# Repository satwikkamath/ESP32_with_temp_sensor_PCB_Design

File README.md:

# ESP32-S3 PCB Design with Temperature Sensor and RGB LED

## Overview

This project focuses on designing a custom PCB using the **ESP32-S3-MINI-1-N8** microcontroller. The PCB integrates an **ENS210** temperature and humidity sensor, a **WS2812B RGB LED** for visual feedback, and a power regulation system using the **TLV75801 LDO** voltage regulator. The design also includes **TVS protection diodes** for USB input safety.

The PCB was designed using **KiCad** and is tailored for applications that require environmental sensing and LED indication, powered through USB with proper surge protection.

## Features

- **ESP32-S3-MINI-1-N8**: A powerful microcontroller for managing sensors, RGB LED, and communication.
- **ENS210 Temperature & Humidity Sensor**: Provides accurate temperature and humidity readings.
- **WS2812B RGB LED**: Addressable LED for visual indication based on temperature readings.
- **TLV75801 LDO Regulator**: Provides a stable 3.3V output from the USB 5V input.
- **USB Surge Protection**: Includes **D3V3XA4B10LP TVS diodes** for protecting the USB input from overvoltage or surge.

## Schematic Design

The schematic was created using **KiCad** and includes the following blocks:

1. **ESP32-S3 Microcontroller**: 
   - Handles the processing and communication.
   - I²C interface to the ENS210 sensor.
   - GPIO control for the WS2812B RGB LED.

2. **ENS210 Temperature & Humidity Sensor**:
   - Connected via the I²C bus.
   - Powered by 3.3V from the regulator.

3. **WS2812B RGB LED**:
   - Data pin connected to GPIO48 of the ESP32.
   - Powered by the 3.3V rail.

4. **TLV75801 LDO**:
   - Regulates 5V USB input to a stable 3.3V output for all components.

5. **TVS Diodes**:
   - Protect the USB power input from surges.

## PCB Layout

The PCB layout includes:

- **Compact design**: Minimizes the space required while keeping all components well-organized.
- **Optimized power and ground planes**: Ensures stable operation and reduces noise.
- **Via stitching**: Improves ground plane integrity.
- **Thermal relief pads**: Used for better heat dissipation where needed.
- **USB Input Protection**: TVS diodes are placed near the USB input to provide surge protection.

# STATUS: ONGOING

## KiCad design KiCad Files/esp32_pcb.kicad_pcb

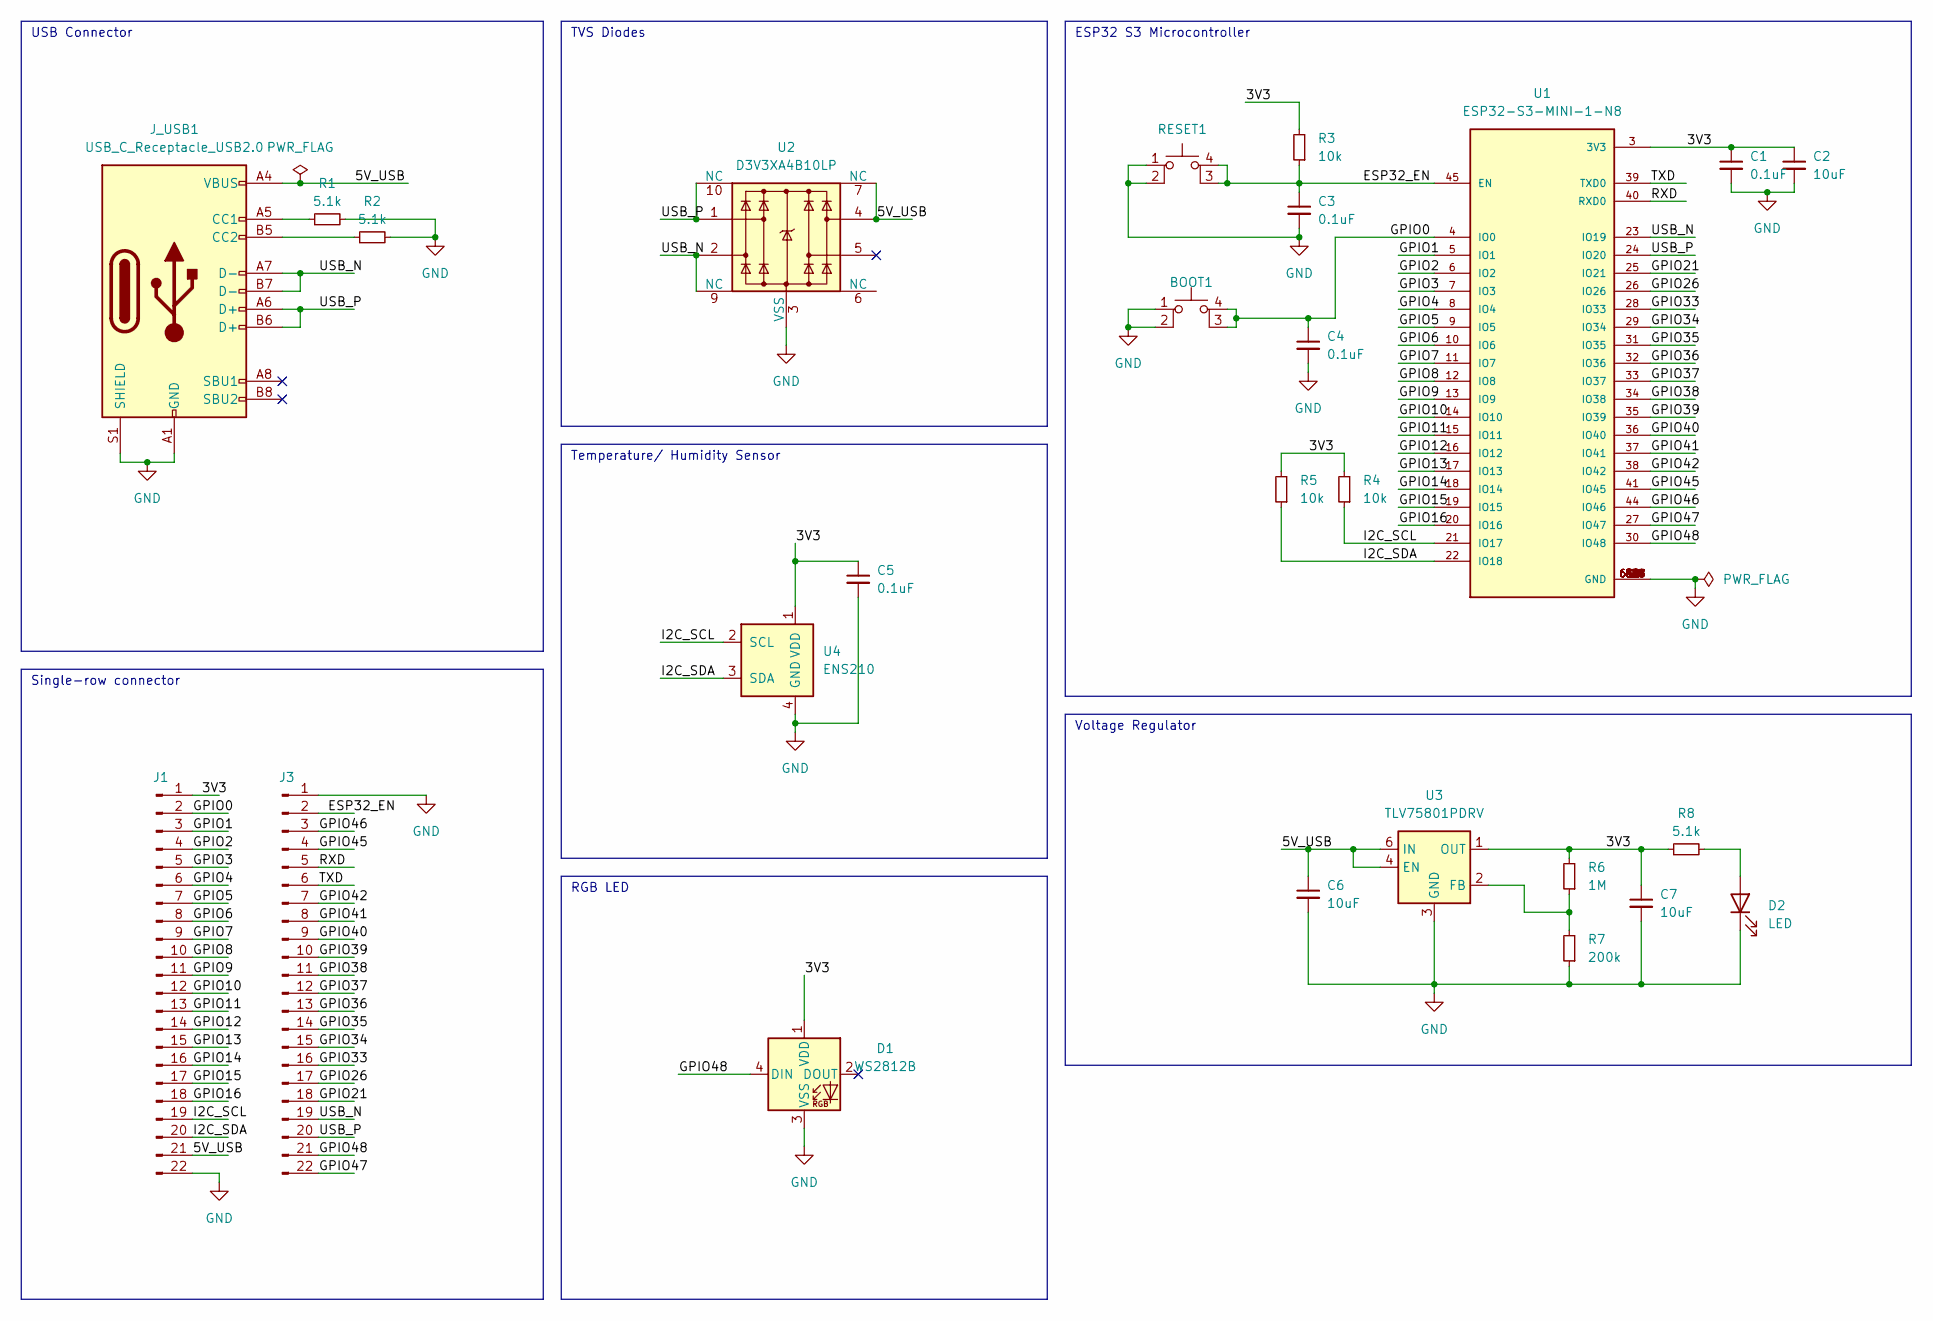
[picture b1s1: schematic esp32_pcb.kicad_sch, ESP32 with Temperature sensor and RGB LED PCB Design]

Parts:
BOOT1: SW_SPST_PTS810
C1, C3, C4, C5: 0.1uF; C_0603_1608Metric
C2, C6, C7: 10uF; C_0603_1608Metric
D1: WS2812B; LED_WS2812B_PLCC4_5.0x5.0mm_P3.2mm
D2: LED; LED_0603_1608Metric
J1: PinHeader_1x22_P2.54mm_Vertical
J3: Conn_01x22_Pin; PinHeader_1x22_P2.54mm_Vertical
J_USB1: USB_C_Receptacle_USB2.0; USB_C_Receptacle_GCT_USB4105-xx-A_16P_TopMnt_Horizontal
R1, R2, R8: 5.1k; R_0603_1608Metric
R3, R4, R5: 10k; R_0603_1608Metric
R6: 1M; R_0603_1608Metric
R7: 200k; R_0603_1608Metric
RESET1: SW_SPST_PTS810
U1: ESP32-S3-MINI-1-N8; XCVR_ESP32-S3-MINI-1-N8; PARTREV v0.6
U2: D3V3XA4B10LP; Diodes_UDFN-10_1.0x2.5mm_P0.5mm
U3: TLV75801PDRV; WSON-6-1EP_2x2mm_P0.65mm_EP1x1.6mm
U4: ENS210; AMS_QFN-4-1EP_2x2mm_P0.95mm_EP0.7x1.6mm

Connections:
/3V3: C1.1, C2.1, C5.1, C7.1, D1.1 (VDD), J1.1, R3.2, R4.2, R5.2, R6.2, R8.1, U1.3 (3V3), U3.1 (OUT), U4.1 (VDD)
/5V_USB: C6.1, J1.21, J_USB1.A4 (VBUS), J_USB1.A9 (VBUS), J_USB1.B4 (VBUS), J_USB1.B9 (VBUS), U2.4, U2.7 (NC), U3.4 (EN), U3.6 (IN)
/ESP32_EN: C3.1, J3.2, R3.1, RESET1.3 (K), RESET1.4 (A), U1.45 (EN)
/GPIO0: BOOT1.3 (K), BOOT1.4 (A), C4.1, J1.2, U1.4 (IO0)
/GPIO1: J1.3, U1.5 (IO1)
/GPIO2: J1.4, U1.6 (IO2)
/GPIO3: J1.5, U1.7 (IO3)
/GPIO4: J1.6, U1.8 (IO4)
/GPIO5: J1.7, U1.9 (IO5)
/GPIO6: J1.8, U1.10 (IO6)
/GPIO7: J1.9, U1.11 (IO7)
/GPIO8: J1.10, U1.12 (IO8)
/GPIO9: J1.11, U1.13 (IO9)
/GPIO10: J1.12, U1.14 (IO10)
/GPIO11: J1.13, U1.15 (IO11)
/GPIO12: J1.14, U1.16 (IO12)
/GPIO13: J1.15, U1.17 (IO13)
/GPIO14: J1.16, U1.18 (IO14)
/GPIO15: J1.17, U1.19 (IO15)
/GPIO16: J1.18, U1.20 (IO16)
/GPIO21: J3.18, U1.25 (IO21)
/GPIO26: J3.17, U1.26 (IO26)
/GPIO33: J3.16, U1.28 (IO33)
/GPIO34: J3.15, U1.29 (IO34)
/GPIO35: J3.14, U1.31 (IO35)
/GPIO36: J3.13, U1.32 (IO36)
/GPIO37: J3.12, U1.33 (IO37)
/GPIO38: J3.11, U1.34 (IO38)
/GPIO39: J3.10, U1.35 (IO39)
/GPIO40: J3.9, U1.36 (IO40)
/GPIO41: J3.8, U1.37 (IO41)
/GPIO42: J3.7, U1.38 (IO42)
/GPIO45: J3.4, U1.41 (IO45)
/GPIO46: J3.3, U1.44 (IO46)
/GPIO47: J3.22, U1.27 (IO47)
/GPIO48: D1.4 (DIN), J3.21, U1.30 (IO48)
/I2C_SCL: J1.19, R4.1, U1.21 (IO17), U4.2 (SCL)
/I2C_SDA: J1.20, R5.1, U1.22 (IO18), U4.3 (SDA)
/RXD: J3.5, U1.40 (RXD0)
/TXD: J3.6, U1.39 (TXD0)
/USB_N: J3.19, J_USB1.A7 (D-), J_USB1.B7 (D-), U1.23 (IO19), U2.2, U2.9 (NC)
/USB_P: J3.20, J_USB1.A6 (D+), J_USB1.B6 (D+), U1.24 (IO20), U2.1, U2.10 (NC)
GND: BOOT1.1, BOOT1.2, C1.2, C2.2, C3.2, C4.2, C5.2, C6.2, C7.2, D1.3 (VSS), D2.1 (K), J1.22, J3.1, J_USB1.A1 (GND), J_USB1.A12 (GND), J_USB1.B1 (GND), J_USB1.B12 (GND), J_USB1.S1 (SHIELD), R1.2, R2.2, R7.1, RESET1.1, RESET1.2, U1.1 (GND), U1.2 (GND), U1.42 (GND), U1.43 (GND), U1.46 (GND), U1.47 (GND), U1.48 (GND), U1.49 (GND), U1.50 (GND), U1.51 (GND), U1.52 (GND), U1.53 (GND), U1.54 (GND), U1.55 (GND), U1.56 (GND), U1.57 (GND), U1.58 (GND), U1.59 (GND), U1.60 (GND), U1.61 (GND), U1.61_1 (GND), U1.61_2 (GND), U1.61_3 (GND), U1.61_4 (GND), U1.61_5 (GND), U1.61_6 (GND), U1.61_7 (GND), U1.61_8 (GND), U1.62 (GND), U1.63 (GND), U1.64 (GND), U1.65 (GND), U2.3 (VSS), U2.8 (VSS), U3.3 (GND), U3.7 (GND), U4.4 (GND), U4.5 (GND)
unnamed: D2.2 (A), R8.2
unnamed: J_USB1.A5 (CC1), R1.1
unnamed: J_USB1.B5 (CC2), R2.1
unnamed: R6.1, R7.2, U3.2 (FB)

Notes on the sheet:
Temperature/ Humidity Sensor
USB Connector
RGB LED
ESP32 S3 Microcontroller
TVS Diodes
Single-row connector
Voltage Regulator

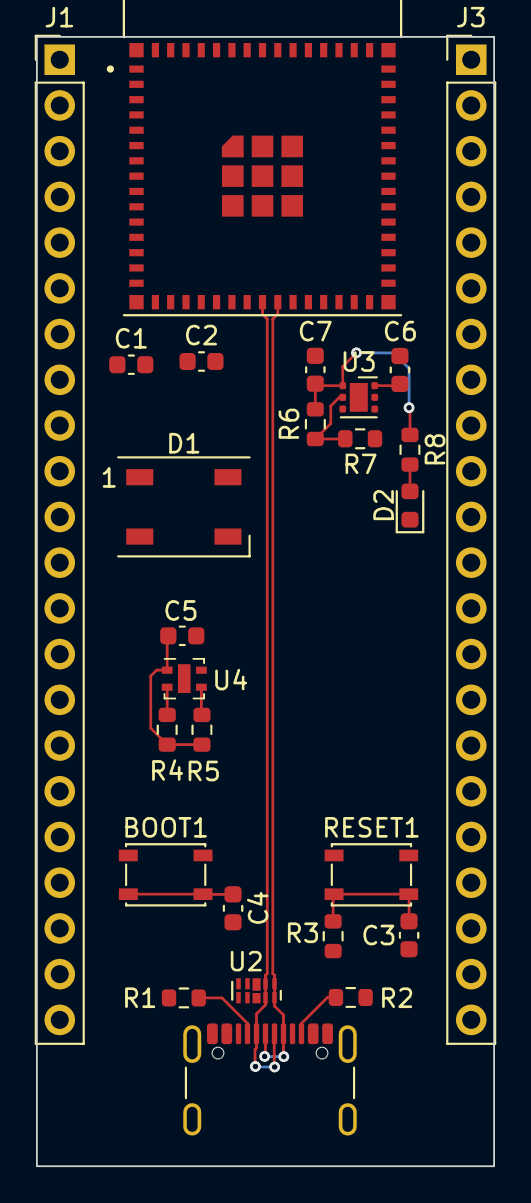
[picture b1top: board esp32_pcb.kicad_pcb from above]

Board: 4 copper layers, 25.4 x 62.7 mm, 26 parts (0 on the bottom side), 47 nets.
